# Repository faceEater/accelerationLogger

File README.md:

A pre-release of my acceleration logger files for critique
	Not guaranteed to work!
	All licensed under CC-BY-SA 3.0

Summary:
    Dimensions: 1.25in x 2.5in * 1in
    Induction charged. Supercapacitor is charged by LT1618 from the coil(P2) and Bridge rectifier.
    Optical communications, serial@56kbaud
    Mating charging/comms circuit not yet designed
    Updatable firmware
    8Mbyte onboard flash
    Charges in <5 minutes with coil supplying 5v at a yet to be determined current (depends on charger)
    Powered from 5V, 5F supercap with LT1615-1 SEPIC Converter
    Linear postregulator for low noise
    Quiescent current < 200uA
    May or may not be potted, depending on requirements. Potted version is watertight.
    P1 for programming AVR + 2 GPIO & Serial
    Low power: <3mA at 1ksps for >30min battery life
    Fast sampling: 3 axis sampling at 1ksps/Axis
    3-axis
    200g full-scale, 100mg resolution 16-200g
    Sub 16-g resolution better than 5 mg
    4-layer board, believed to meet OSH park's design rules
    (Mostly) Arduino-compatible
    Atmega1284p processor
    Open Source -- CC-BY-SA 3.0

Github: https://github.com/faceEater/accelerationLogger

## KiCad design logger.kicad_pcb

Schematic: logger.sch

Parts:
C2, C3: 22pf; SM0603_Capa
C4: 1uF; SM0603_Capa
C5, C12: 4.7u; SM0805
C6, C10, C27, C28: 1u; SM0603_Capa
C7: 4.7pF; SM0603_Capa
C8: .1u; SM0603_Capa
C9, C11, C13, C14, C29: 10u; SM0805
C23, C24, C25: 1n; SM0603_Capa
C26: C; SM0603_Capa
C30: 1u
D1: DIODESCH; SOD323
IC1: ATMEGA1284P-A; TQFP44
L1, L2, L5: 10u; SM2010
P1: CONN_5X2; PIN_ARRAY_5x2
Q1: MOS_P
R1, R5, R6, R7, R8, R9, R10, R12, R15, R18: 100k; SM0603
R2, R3: 1M; SM0603
R4: 560k; SM0603
R11, R30: 1; SM0603
R13, R14, R16: 196k; SM0603
R17: 180k; SM0603
R20: 1M
R31: 1k
U1: LT1615-1; SOT23-5
U2: SST25VF064C
U3: MCP6054; SO14N
U4: MAX11613; uMAX8
U5: TPS7703X; SOT23-5
U6: ADXL337; LFCSP8
U7: LIS3DSH; LGA16
X1: CRYSTAL; XTAL_DFN_CTS403

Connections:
3V3: C4.2, C7.1, C9.1, C10.1, C27.2, C28.2, C30.1, D1.2 (K), IC1.5 (VCC), IC1.17 (VCC), IC1.27 (AVCC), IC1.38 (VCC), L5.1, P1.2, R3.1, R5.2, R6.2, R12.2, U2.3 (!WP), U2.7 (!RESET), U2.8 (Vcc), U7.1 (Vdd_IO); also elsewhere on the board
3V3_Analog: C8.1, C13.1, Q1.D, R18.1, U3.4 (V+), U4.4 (Ain3), U6.14 (Vs), U6.15 (Vs)
3V3_Analog_Unswitched: C11.1, C14.2, Q1.S, R7.2, R8.2, R20.1, R30.2, U4.5 (V+), U7.8 (CS), U7.14 (Vdd), U7.15 (Res)
GND: C2.1, C3.1, C4.1, C5.2, C8.2, C9.2, C10.2, C11.2, C12.2, C13.2, C14.1, C23.2, C24.2, C25.1, C26.2, C27.1, C28.1, C29.2, C30.2, IC1.6 (GND), IC1.18 (GND), IC1.28 (GND), IC1.39 (GND), L2.2, P1.6, R4.2, R13.2, R14.2, R15.2, R17.2, U1.2 (GND), U2.4 (GND), U3.11 (GND), U4.6 (Gnd), U5.2 (GND), U5.3 (!EN), U6.2 (ST), U6.6 (GND), U6.7 (GND), U7.5 (GND), U7.7 (SEL), U7.10 (Res), U7.12 (GND), U7.13 (GND), U7.16 (GND); also elsewhere on the board
unnamed: C2.2, IC1.7 (XTAL2), R2.1, X1.2
unnamed: C3.2, IC1.8 (XTAL1), R2.2, X1.1
unnamed: C6.1, L1.2, U1.1 (SW)
unnamed: C6.2, D1.1 (A), L2.1
unnamed: C7.2, R3.2, R4.1, U1.3 (FB)
unnamed: C12.1, R11.2
unnamed: C23.1, R10.1, U6.4 (Yout)
unnamed: C24.1, R9.1, U6.16 (Zout)
unnamed: C25.2, R16.1, U6.5 (Xout)
unnamed: C26.1, IC1.29 (AREF)
unnamed: C29.1, L5.2, U5.1 (IN)
unnamed: IC1.1 ((PCINT13/MOSI)PB5), P1.4, R12.1, U2.5 (SI)
unnamed: IC1.2 ((PCINT14/MISO)PB6), P1.1, R6.1, U2.2 (SO)
unnamed: IC1.3 ((PCINT15/SCK)PB7), P1.3, R5.1, U2.6 (SCK)
unnamed: IC1.4 (~RESET), P1.5, R1.1
unnamed: IC1.19 ((PCINT16/SCL)PC0), R7.1, U4.8 (SCL), U7.4 (SCL)
unnamed: IC1.20 ((PCINT17/SDA)PC1), R8.1, U4.7 (SDA), U7.6 (SDA)
unnamed: IC1.23 ((PCINT20/TDO)PC4), U7.11 (INT1)
unnamed: IC1.24 ((PCINT21/TDI)PC5), R31.2
unnamed: IC1.30 ((PCINT7/ADC7)PA7), P1.10
unnamed: IC1.31 ((PCINT6/ADC6)PA6), P1.9
unnamed: IC1.44 ((PCINT12/OC0B/~SS~)PB4), U2.1 (!CS)
unnamed: Q1.G, R20.2, R31.1
unnamed: R10.2, R14.1, U3.12 (VinC+)
unnamed: R11.1, R30.1, U5.5 (OUT)
unnamed: R9.2, R13.1, U3.10 (VinD+)
unnamed: R15.1, R16.2, U3.3 (InA+)
unnamed: R17.1, R18.2, U3.5 (VinB+)
unnamed: U3.1 (VoutA), U3.2 (InA-), U4.1 (Ain0)
unnamed: U3.6 (VinB-), U3.7 (VoutB)
unnamed: U3.8 (VoutD), U3.9 (VinD-), U4.3 (Ain2)
unnamed: U3.13 (VinC-), U3.14 (VoutC), U4.2 (Ain1)
RX: IC1.9 ((PCINT24/RXD0)PD0), P1.8; also elsewhere on the board
Reset: R1.2; also elsewhere on the board
TX: IC1.10 ((PCINT25/TXD0)PD1), P1.7; also elsewhere on the board
Vcap: C5.1, L1.1, U1.4 (!SHDN), U1.5 (Vin); also elsewhere on the board
Vmon: IC1.37 ((PCINT0/ADC0)PA0); also elsewhere on the board

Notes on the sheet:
1% or better for FB resistors
Select TPS77033 closest to but not exceeding .1v less than the LT1651 output (Or tweak FB resistors)
Rugged 250g, 3axis, 1Ksps acceleration logger: 4Mbyte flash, 5v 5F Supercap
1-6:ISP 7-8:TX,RX 9-10: GPIO
Using linear reg for noise reduction: do not substitute!
OSHW CC-BY-SA 3.0

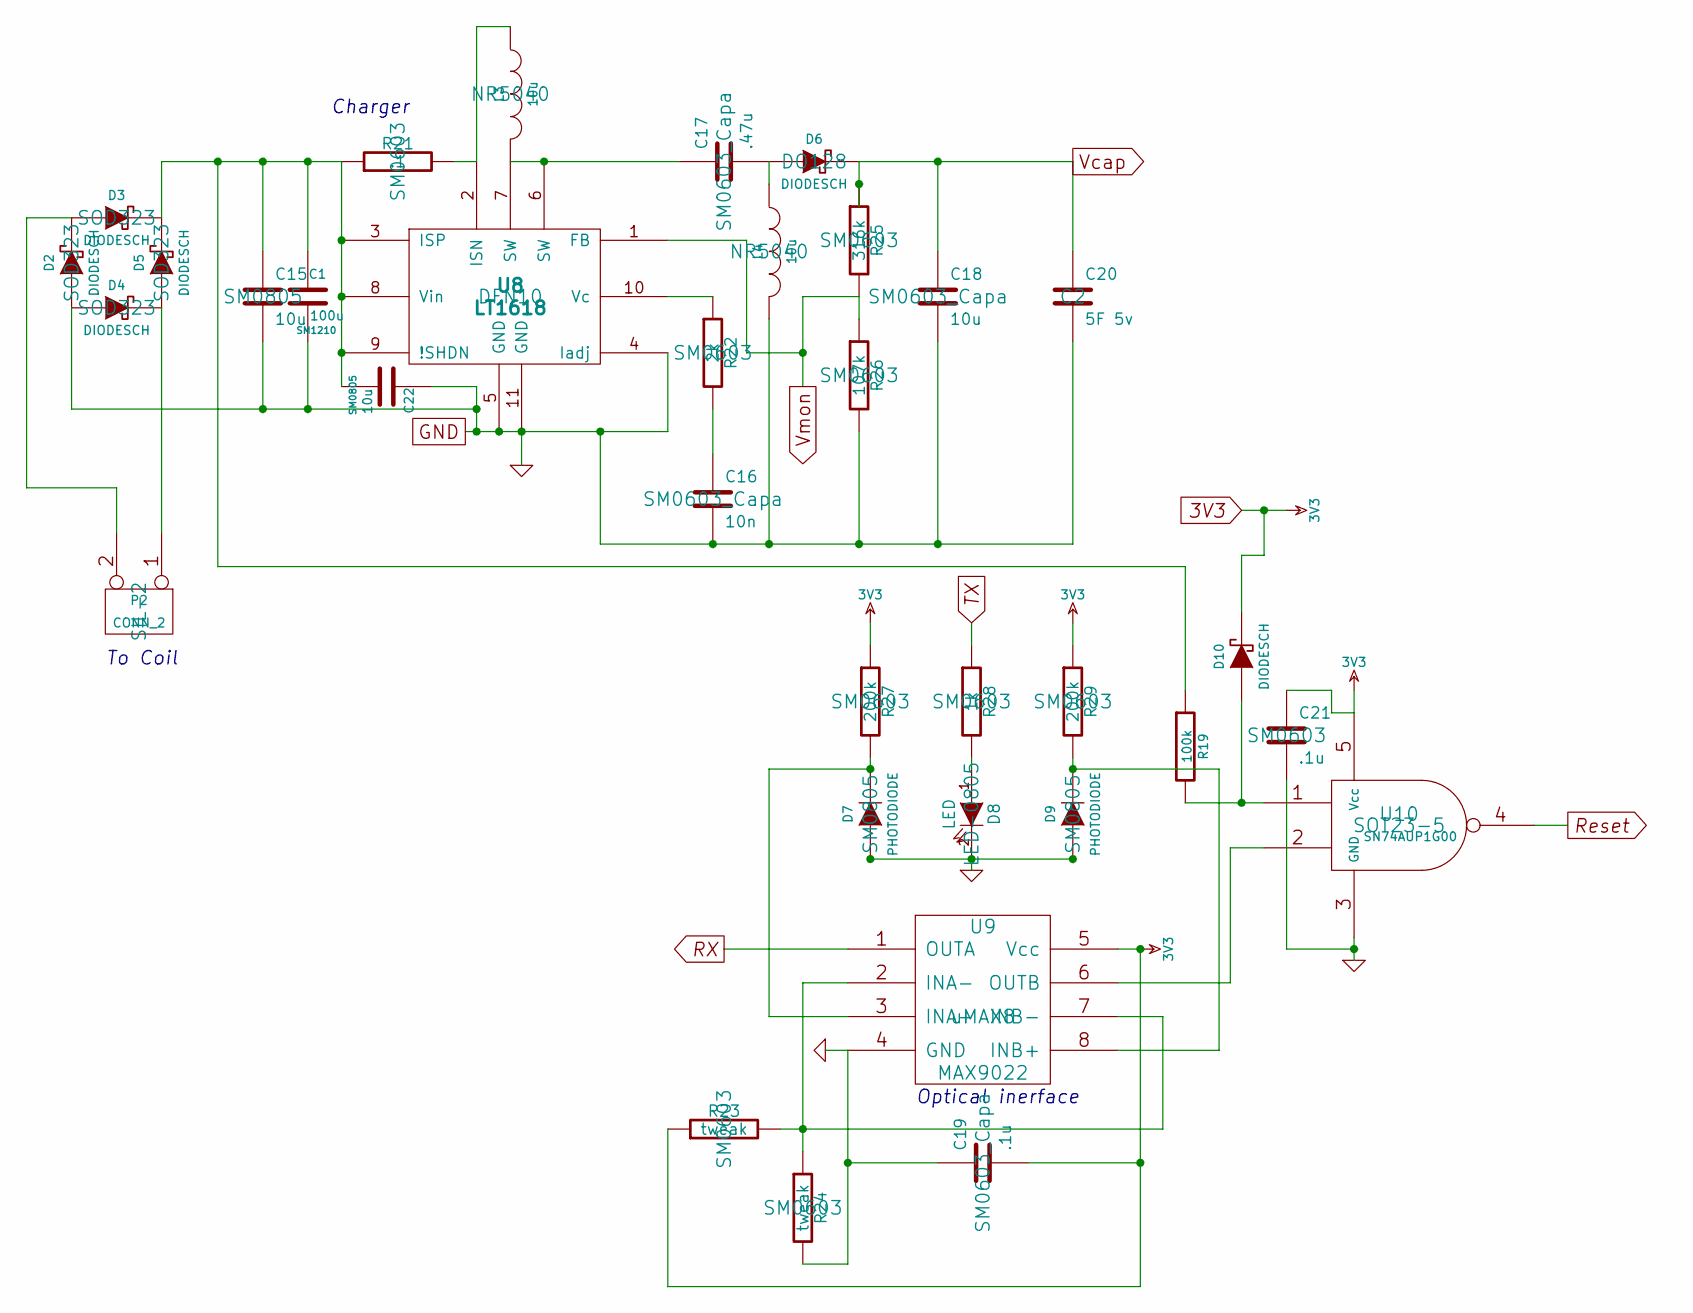
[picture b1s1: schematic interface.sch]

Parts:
C1: 100u; SM1210
C15, C22: 10u; SM0805
C16: 10n; SM0603_Capa
C17: .47u; SM0603_Capa
C18: 10u; SM0603_Capa
C19: .1u; SM0603_Capa
C20: 5F 5v; C2
C21: .1u; SM0603
D2, D3, D4, D5: DIODESCH; SOD323
D6: DIODESCH; DO128
D7, D9: PHOTODIODE; SM0805
D8: LED; LED-0805
D10: DIODESCH
L3, L4: 10u; NR5040
P2: CONN_2; SIL-2
R19: 100k
R21: .1; SM0603
R22: 2k; SM0603
R23, R24: tweak; SM0603
R25: 316k; SM0603
R26: 107k; SM0603
R27, R29: 200k; SM0603
R28: 1k; SM0603
U8: LT1618; DFN10
U9: MAX9022; uMAX8
U10: SN74AUP1G00; SOT23-5

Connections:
3V3: C19.2, C21.1, D10.2 (K), R23.1, R27.1, R29.1, U9.5 (Vcc), U10.5 (Vcc); also elsewhere on the board
GND: C1.2, C15.2, C16.2, C18.2, C19.1, C20.2, C21.2, C22.1, D2.1 (A), D4.1 (A), D7.1 (A), D8.2 (K), D9.1 (A), L4.2, R24.2, R26.2, U8.4 (Iadj), U8.5 (GND), U8.11 (GND), U9.4 (GND), U10.3 (GND); also elsewhere on the board
unnamed: C1.1, C15.1, C22.2, D3.2 (K), D5.2 (K), R19.1, R21.1, U8.3 (ISP), U8.8 (Vin), U8.9 (!SHDN)
unnamed: C16.1, R22.2
unnamed: C17.1, L3.2, U8.6 (SW), U8.7 (SW)
unnamed: C17.2, D6.1 (A), L4.1
unnamed: D2.2 (K), D3.1 (A), P2.2 (PM)
unnamed: D4.2 (K), D5.1 (A), P2.1
unnamed: D7.2 (K), R27.2, U9.3 (INA+)
unnamed: D8.1 (A), R28.2
unnamed: D9.2 (K), R29.2, U9.8 (INB+)
unnamed: D10.1 (A), R19.2, U10.1
unnamed: L3.1, R21.2, U8.2 (ISN)
unnamed: R22.1, U8.10 (Vc)
unnamed: R23.2, R24.1, U9.2 (INA-), U9.7 (INB-)
unnamed: U9.6 (OUTB), U10.2
RX: U9.1 (OUTA); also elsewhere on the board
Reset: U10.4; also elsewhere on the board
TX: R28.1; also elsewhere on the board
Vcap: C18.1, C20.1, D6.2 (K), R25.1; also elsewhere on the board
Vmon: R25.2, R26.1, U8.1 (FB); also elsewhere on the board

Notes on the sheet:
To Coil
Optical inerface
Charger

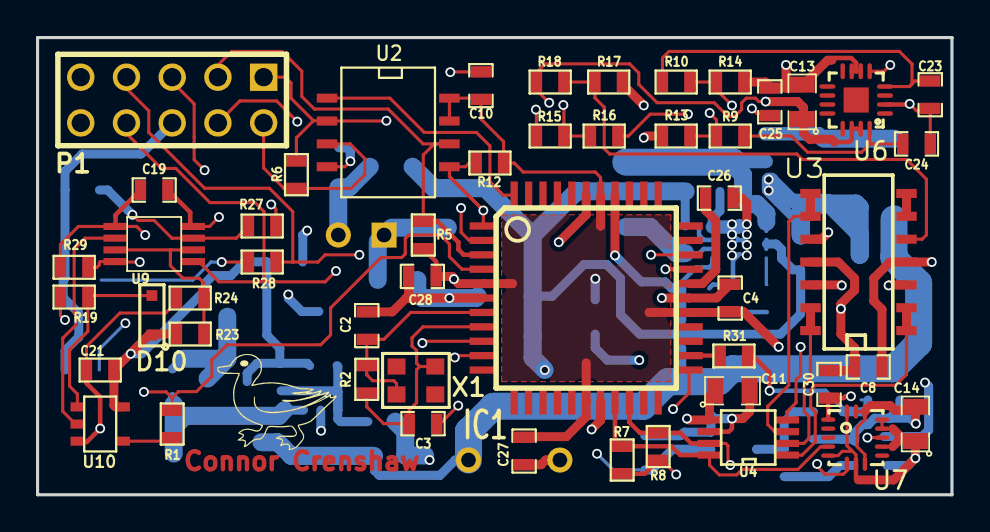
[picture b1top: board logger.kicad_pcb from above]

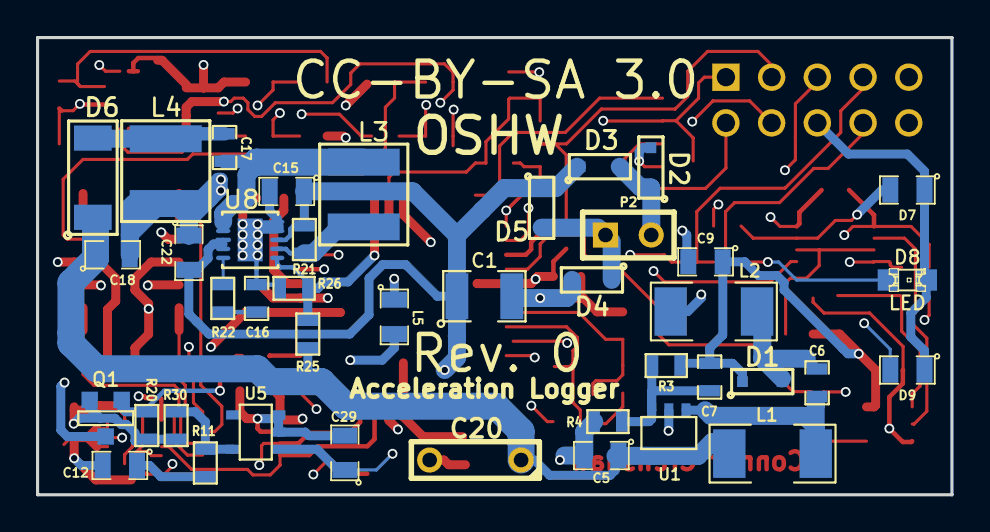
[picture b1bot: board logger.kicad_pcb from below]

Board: 4 copper layers, 50.8 x 25.4 mm, 92 parts (41 on the bottom side), 55 nets.

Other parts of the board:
VAL: DUCK

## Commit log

2013-11-10 General layout/grounding tweaks, DC-DC layout improved, ADC set up for Vdd as ref, switchable 3v3_Analog for lower standby power, reset circuitry redone, Footprint fixes, better silkscreen.
